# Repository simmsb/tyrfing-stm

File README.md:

# Hardware and firmware for my flashlight drivers that use stm32L0 processors

This repo contains the KiCad files of my self-designed flashlight driver (stm32L0, using a MP3432 boost driver) and the Rust firmware for it.

Mostly based off my [AVR flashlight firmware](https://github.com/simmsb/tyrfing/), also written in Rust.

# Running and flashing

To run with debug logging: `env DEFMT_LOG="debug" cargo run`
To flash a non-debug build: `env DEFMT_LOG="off" cargo run --no-default-features --features default_no_debug --release`

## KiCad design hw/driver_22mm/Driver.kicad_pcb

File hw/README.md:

# Hardware stuff

This folder contains the kicad schematic and layout for the driver, and
`boost.nbt` which is all the potential divider calculations, written in
[numbat](https://github.com/sharkdp/numbat).

# Changelog

- v0: Initial design: had the mistake of using the Rds(on) of a FET as a sense
  resistor... that's a bad idea, don't do it.
  
- v1: Second revision: uses a real sense resistor to measure the high end
  current, and an analog mux to switch between measuring before the low end
  sense resistor, or the high end sense resistor (such that we don't measure
  Rds(on) + Rsense).
  
  I also changed the LDO from 2.5v to 2.8v
  
- v2: Third revision: Adds more current return path vias, but makes the spring
  pad off center (I have no idea if this will work)
  
# Issues I think I still have

1. As of v1 I am not completely happy with the current return path after the
   sense resistors, currently there are vias spammed everywhere possible but I'm
   not sure there's enough. With v2 I added more vias and moved the spring pad
   off center, but that sounds dumb.

# Thanks

This video series:
https://www.youtube.com/playlist?list=PLYK5tmZIBWtEJjwAFE-49hSeELu9zoAmV was a
great help with getting started designing the current controlled boost circuit.

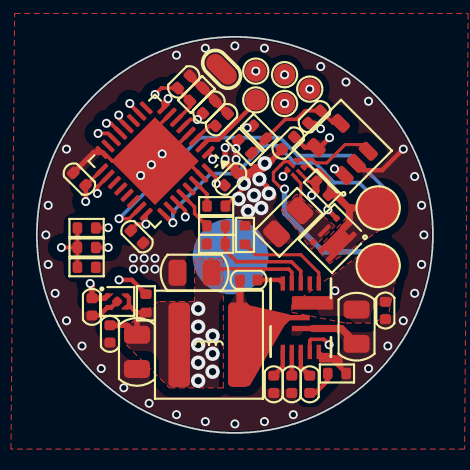
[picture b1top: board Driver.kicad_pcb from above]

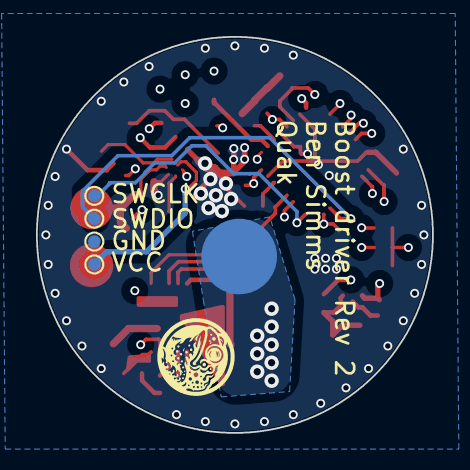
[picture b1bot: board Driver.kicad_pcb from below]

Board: 4 copper layers, 22.0 x 22.0 mm, 51 parts (4 on the bottom side), 33 nets.

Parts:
C1, C3, C13: 47uF; C_0805_2012Metric
C4, C16, C20: 4.7uF; C_0402_1005Metric
C5: 22nF; C_0402_1005Metric
C6, C8, C10, C14, C15, C17, C18: 100nF; C_0402_1005Metric
C7: 3.3nF; C_0402_1005Metric
C9: 6.8nF; C_0402_1005Metric
C19: 10uF; C_0402_1005Metric
C21: 1nF; C_0402_1005Metric
J1: +LED; TestPoint_Pad_D2.0mm
J2: -LED; TestPoint_Pad_D2.0mm
J3: Button LED; TestPoint_Pad_D1.0mm
J4: Wire GND; TestPoint_Pad_D1.0mm_copy
J5: SWDIO; TestPoint_Pad_D0.7mm
J6: SWCLK; TestPoint_Pad_D0.7mm
J7: GND; TestPoint_Pad_D0.7mm
J8: VCC; TestPoint_Pad_D0.7mm
J9: B; TestPoint_Pad_D1.0mm
J10: R; TestPoint_Pad_D1.0mm
J11: G; TestPoint_Pad_D1.0mm
J12: Button; TestPoint_Pad_D1.0mm
L1: 1.3uH; L_Coilcraft_XAL5030
Q1: Vishay_PowerPAK_SC70-6L_Single
R1: 20k - R_UVLO_BOTTOM; R_0402_1005Metric
R2: 24k - R_UVLO_BOTTOM; R_0402_1005Metric
R3: 285k - R_DAC_TOP; R_0402_1005Metric
R4: 3.3K - R_DAC_BOTTOM1; R_0402_1005Metric
R5: 10m - R_SENSE_MAIN; R_0805_2012Metric
R6: 4R - R_SENSE_HDR; R_0402_1005Metric
R7: 27k; R_0402_1005Metric
R8: 6.8k; R_0402_1005Metric
R9: 750k - R_FB_A; R_0402_1005Metric
R10: 75k - R_FB_B; R_0402_1005Metric
R11: 434k - R_FB_C; R_0402_1005Metric
R12: 10k; R_0402_1005Metric
R13: 1.6M - R_BAT_TOP; R_0402_1005Metric
R14: 3M - R_BAT_BOT; R_0402_1005Metric
U1: MP3431GL-P; QFN-13_MP3431_MNP
U2: OPA333AIDBV; SOT-23-5
U3: STM32L072KBUx; QFN-32-1EP_5x5mm_P0.5mm_EP3.45x3.45mm
U4: NCP114AMX280TCG; UDFN-4-1EP_1x1mm_P0.65mm_EP0.48x0.48mm
U5: XS3A1T3157GSH; XSON6_SOT1202_NEX

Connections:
+BATT: C1.1, C3.1, C16.1, L1.1, R13.1, U1.12 (VIN), U4.3 (EN), U4.4 (IN)
/-LED: J2.1, Q1.1 (D), R6.1, U5.3 (Y1)
/BAT_SENSE: C21.1, R13.2, R14.1, U3.6 (PA0)
/BOOST_EN: R1.1, U3.28 (PB6)
/DAC: R3.1, U3.10 (PA4)
/FB: R9.2, R10.1, R11.2, U1.5 (FB)
/HDR: Q1.3 (G), U3.8 (PA2)
/OPAMP_EN: C8.2, U2.5 (V+), U3.27 (PB5)
/SHUNT_SELECT: U3.1 (PC14), U5.6 (S)
/SWCLK: J6.1, U3.25 (PA14)
/SWDIO: J5.1, U3.23 (PA13)
GND: C1.2, C3.2, C4.2, C5.2, C8.1, C10.2, C13.2, C14.2, C15.1, C16.2, C17.1, C18.1, C19.1, C20.2, C21.2, J4.1, J7.1, R2.2, R4.2, R5.2, R6.2, R7.2, R8.2, R10.2, R12.2, R14.2, U1.6 (AGND), U1.7 (PGND), U2.2 (V-), U3.4 (VSSA), U3.7 (PA1), U3.16 (VSS), U3.31 (VSS), U3.33 (VSS), U4.2 (GND), U4.5 (GND), U5.2 (GND)
unnamed: C7.2, R11.1, U2.1
unnamed: C9.2, R8.1
unnamed: J3.1, U3.2 (PC15)
unnamed: J9.1, U3.14 (PB0)
unnamed: J10.1, U3.12 (PA6)
unnamed: J11.1, U3.13 (PA7)
unnamed: J12.1, U3.18 (PA8)
unnamed: Q1.4 (S), R5.1, U5.1 (Y2)
unnamed: C6.2, U1.13 (BST)
unnamed: C9.1, U1.4 (COMP)
unnamed: R1.2, R2.1, U1.11 (EN)
unnamed: R7.1, U1.9 (ILIM)
unnamed: C5.1, U1.3 (SS)
unnamed: C6.1, L1.2, U1.1 (SW)
unnamed: C4.1, U1.2 (VDD)
unnamed: U2.3 (+), U5.4 (Z)
unnamed: C7.1, R3.2, R4.1, U2.4 (-)
unnamed: R12.1, U3.30 (BOOT0)
unnamed: C14.1, U3.3 (NRST)
VCC: C15.2, C17.2, C18.2, C19.2, C20.1, J8.1, U3.5 (VDDA), U3.17 (VDD), U3.24 (VDD_USB), U3.32 (VDD), U4.1 (OUT), U5.5 (VCC)
VPP: C10.1, C13.1, J1.1, R9.1, U1.8 (VOUT)

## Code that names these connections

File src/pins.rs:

macro_rules! define_pin {
    ($name:ident, $p:ident) => {
        #[allow(unused)]
        macro_rules! $name {
            () => {
                ::embassy_stm32::peripherals::$p
            };
        }

        ::paste::paste! {
            #[allow(unused)]
            macro_rules! [<take_ $name>] {
                ($pins:expr) => {
                    $pins.$p
                }
            }

            #[allow(unused)]
            pub(crate) use [<take_ $name>];
        }

        #[allow(unused)]
        pub(crate) use $name;
    };
}

define_pin!(battery_sense, PA0);
define_pin!(hdr, PA2);

#[cfg(feature = "board_dev")]
define_pin!(en, PA3);
#[cfg(feature = "board_v0")]
define_pin!(en, PB5);

#[cfg(feature = "board_v1")]
define_pin!(opamp_en, PB5);
#[cfg(feature = "board_v1")]
define_pin!(boost_en, PB6);
#[cfg(feature = "board_v1")]
define_pin!(shunt_select, PC14);

define_pin!(dac, PA4);
define_pin!(aux_r, PA6);
define_pin!(aux_g, PA7);
define_pin!(aux_b, PB0);
define_pin!(button_led, PC15);
define_pin!(button, PA8);

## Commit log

2024-05-26 Stuff
2024-06-02 Try out maitake
2024-06-02 More information
2024-06-02 Disable the output buffer on the DAC
2024-06-11 Format
2024-06-11 More accurate battery percentage
    Linearly interpolate given control points
2024-06-11 Add croaking mode
2024-06-12 Abstract out repeated level adjustment clauses in each mode
2024-06-12 Fade out when depressing switch in lockout mode
2024-06-18 Driver v2 changes
2024-07-07 Update battery voltage divider
2024-09-22 Push changes
2024-09-22 Add hw render
